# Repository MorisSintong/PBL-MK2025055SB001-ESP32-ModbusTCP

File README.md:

# PBL-MK2025055SB001 - Face Detection & Assembly Station SCADA

Project-Based Learning (PBL) repository for a SCADA prototype built around the
**Assembly Station** at Politeknik Negeri Batam (POLIBATAM). The system uses an
**ESP32-S3** and a **Mitsubishi FX5U PLC** as the main components, communicating
over **Modbus TCP/IP** through a W5500 Ethernet module, with a PC-based face
recognition interface acting as the human-machine interface (HMI) and access
controller.

The main objective is to develop an automatic control & monitoring system for
the Assembly Station that:

- Can be accessed over **Wi-Fi** by external devices (PC, mobile, HMI).
- Talks to the **FX5U PLC** via **Modbus TCP/IP** through the ESP32 (Modbus
  server on port 503).
- Performs **face recognition** on the PC (OpenCV/LBPH) and only allows
  authorized operators to start the machine.
- Provides a web HMI with live video feed, status indicators, and start/stop/\
  emergency/reset controls.
- Uses a modern **CMake + Ninja + Xtensa GCC 16.1.0** cross-compilation toolchain
  and host **CTest** simulation harness with zero dependency on PlatformIO or Arduino IDE.

## Repository Layout

| Path | Description |
| --- | --- |
| `Electrical-Schematics/` | KiCad project and rendered images of the electrical wiring (ESP32-S3 + W5500 + PLC I/O). |
| `ESP32-Program/` | Modular C++17 firmware for the ESP32-S3 (CMake + Ninja + Xtensa GCC 16.1.0 + FreeRTOS + Modbus TCP + CTest host suite). |
| `Emulation/` | Multi-node hardware emulation (Virtual ESP32 Bridge, Virtual FX5U PLC, Virtual HMI, Renode) & QoS benchmark suite. |
| `Interface/` | Python (Flask + OpenCV) face-recognition HMI, web front-end, and empirical timing logs (`Timings_log/`). |
| `justfile` | Root task runner orchestrating firmware builds, CTest unit tests, multi-node QoS emulation, and flashing. |
| `test_results.md` | Comprehensive test report compiling CTest unit tests, physical hardware baseline logs, and multi-node emulation QoS metrics. |
| `README.md` | High-level system architecture, repository layout, and quick-start guide. |

## System Architecture
```mermaid
graph TD
    Camera[Camera]
    PC[PC]
    PLC[PLC FX5U]
    Wago[Wago I/O Module]
    ExternalDevice[External Device]
    Output[Output]

    subgraph ESP32Container ["ESP32-S3 Physical Device"]
        ESP32Core(ESP32-S3)
        subgraph HostedServices ["Hosted Services"]
            WebServer[Web Server]
        end
    end

    Camera ---|USB-Serial| PC
    PC ---|HTTP Wi-Fi :80| ESP32Core
    Wago --- Output

    PLC ===|Modbus TCP/IP :503 PLC=Client, ESP32-S3=Server| ESP32Core
    PLC ===|Modbus TCP/IP PLC=Client, Wago=Server| Wago

    WebServer -.->|Wi-Fi| ExternalDevice
```

## System Overview

1. **Interface (PC)** runs a Flask web app (`Interface/app.py` or `Interface/AppImproved.py`) that:
   - Captures the webcam feed and detects faces using Haar cascade.
   - Recognizes the operator using an LBPH model (`trainer/trainer.yml`).
   - On authorized detection, sends HTTP commands to the ESP32
     (`/action?type=start|stop|emergency|reset`) and updates `/user_detection?detected=1|0`.
2. **ESP32-S3** (`ESP32-Program/App/Src/main.cpp`) runs the Modbus bridge & REST gateway:
   - **Wi-Fi & REST API (Core 0)** — receives commands from the PC interface on port 80.
   - **W5500 Ethernet & Modbus TCP server (Core 1)** — serves Modbus TCP on port 503, writes momentary command coils read by the FX5U PLC, and reads status feedback coils from the PLC.
3. **Mitsubishi FX5U PLC** is the Modbus TCP client that controls the Assembly
   Station actuators based on the ESP32 coils.

See the [System Architecture](#system-architecture) section for the full block diagram and the per-directory
`README.md` files for component-level details.

## Quick Start

1. Test, emulate, and flash the firmware using the modern toolchain (`just` + CMake + Ninja + Xtensa GCC / MinGW Clang):
   ```bash
   just test                     # Run host CTest unit test suite (0.04s)
   just build-release            # Cross-compile native ESP32-S3 ELF & firmware.bin
   just emulate-qos samples="50" # Run multi-node SCADA & PLC QoS emulation
   just diag-esptool             # Run silicon flash & security diagnostics on COM10
   just flash-esptool            # Flash ESP32-S3 over UART via uvx esptool @ 921600 baud
   just monitor                  # Serial monitor @ 921600 baud via uvx pyserial
   ```
2. Train the face model from the PC interface:
   ```bash
   cd Interface
   python 01_Ambil_Wajah.py   # capture dataset into dataset/
   python 02_training.py      # train -> trainer/trainer.yml
   ```
3. Launch the web HMI:
   ```bash
   python app.py              # http://<PC-IP>:5000
   ```
4. Configure the PLC (FX5U) Modbus TCP client to connect to the ESP32 Ethernet
   IP (`192.168.1.50:503`) and read/write the coils listed in
   `ESP32-Program/App/Inc/app_config.hpp`.

## Finished Product & Implementation

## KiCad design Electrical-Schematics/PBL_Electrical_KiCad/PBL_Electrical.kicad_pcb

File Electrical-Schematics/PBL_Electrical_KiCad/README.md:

# PBL_Electrical_KiCad

Native KiCad project for the PBL Assembly Station electrical schematic and PCB.

## Preview

## Key files

- `PBL_Electrical.kicad_pro` – KiCad project file (open this in KiCad).
- `PBL_Electrical.kicad_sch` – Schematic sheet.
- `PBL_Electrical.kicad_pcb` – PCB layout.
- `PBL_Electrical.kicad_prl` – KiCad project local settings.
- `PBL_Proj.bak` / `PBL_Proj-sem5.pretty/` / `PBL_Proj.kicad_sym` – Project
  symbol library, custom footprint library, and backups.
- `fp-info-cache`, `fp-lib-table`, `sym-lib-table` – KiCad library tables.
- `PBL_Electrical.png` – Rendered preview of the board/schematic.
- `PBL_Electrical.step` / `PBL_Electrical.wrl` – 3D model exports for CAD.
- `3d.pcb3d` – KiCad 3D viewer cache.
- `PBL_Electrical-backups/` – Automatic KiCad backups.

## How to use

1. Open `PBL_Electrical.kicad_pro` in **KiCad 6+**.
2. Edit the schematic / PCB as needed.
3. Re-export `PBL_Electrical.png` and the 3D models, then update the parent
   `Electrical-Schematics/` images if the wiring changes.

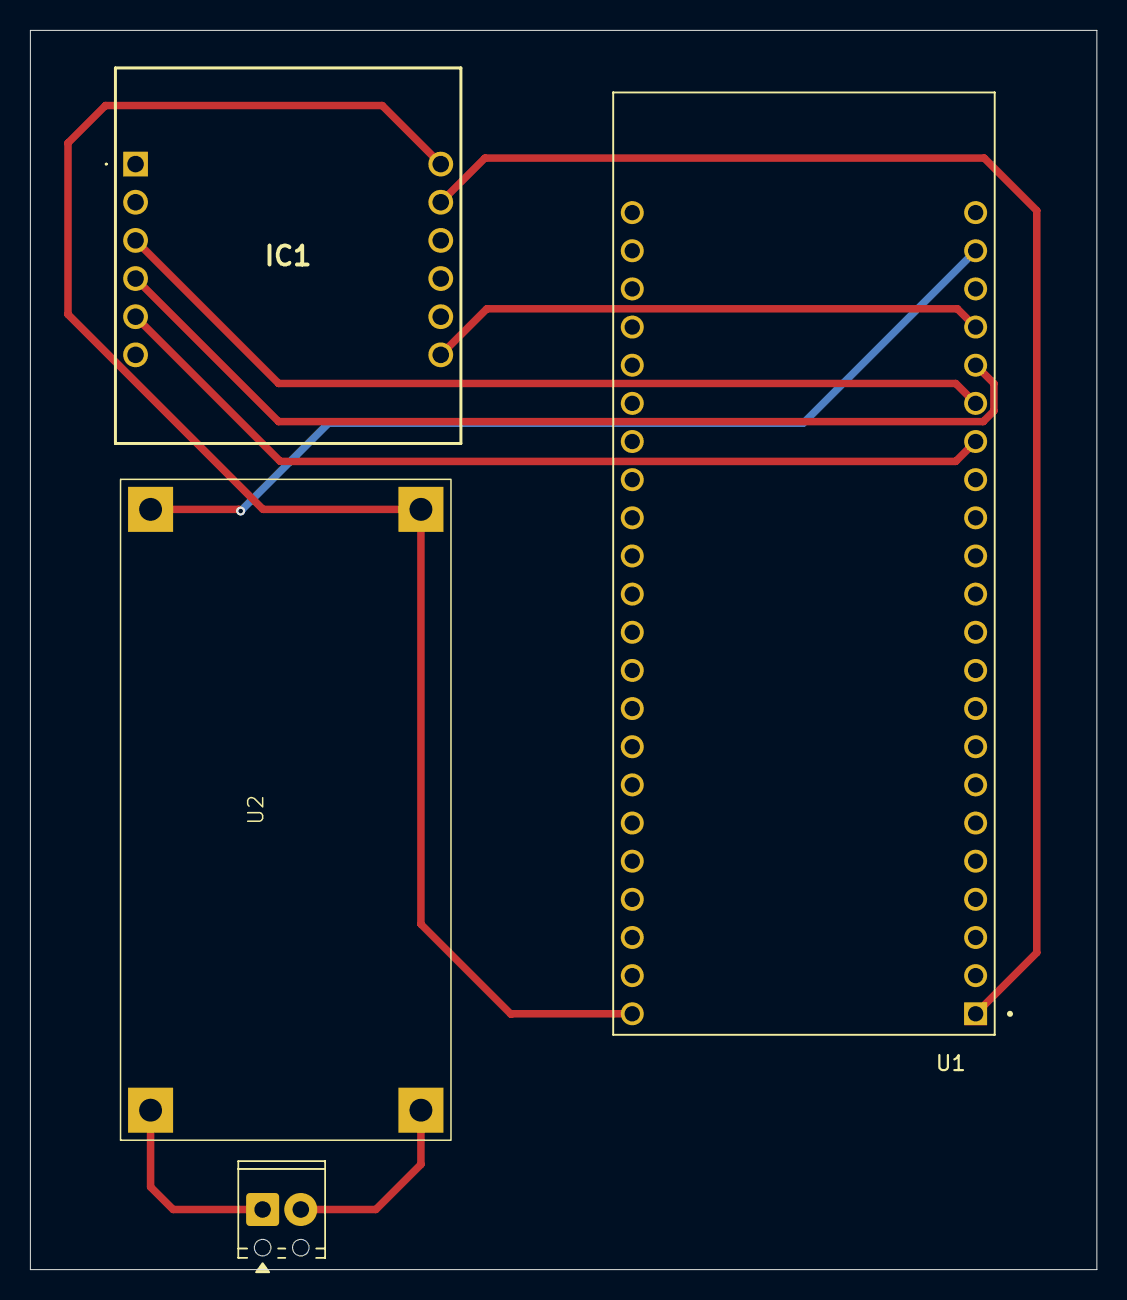
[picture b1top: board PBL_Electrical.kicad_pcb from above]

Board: 2 copper layers, 71.0 x 82.5 mm, 4 parts (0 on the bottom side), 9 nets.

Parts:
IC1: w5500 Module; WIZ850IO
J1: Screw_Terminal_01x02; TerminalBlock_Phoenix_MPT-0,5-2-2.54_1x02_P2.54mm_Horizontal
U1: ESP32-S3-DEVKITC-1-N16R8; ESP32-S3-DEVKITC-1-N8R8
U2: LM2586S Buck-Converter; Untitled

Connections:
+3V3: IC1.J22 (3.3V_1), U1.J1_1 (3V3)
+5V: U1.J1_21 (5V0), U2.3 (OUT+)
+24V: J1.1, U2.1 (IN+)
/ETH_CS: IC1.J15 (SCNN), U1.J1_16 (GPIO10)
/ETH_MISO: IC1.J26 (MISO), U1.J1_19 (GPIO13)
/ETH_MOSI: IC1.J13 (MOSI), U1.J1_17 (GPIO11)
/ETH_SCLK: IC1.J14 (SCLK), U1.J1_18 (GPIO12)
GND: IC1.J21 (GND_3), U1.J3_1 (GND), U2.4 (OUT-)
GND1: J1.2, U2.2 (IN-)

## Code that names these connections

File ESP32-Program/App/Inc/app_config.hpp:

#pragma once

#include <cstddef>
#include <cstdint>

namespace pbl {
namespace config {

// =======================================================================
// HARDWARE SPI & W5500 PIN CONFIGURATION (ESP32-S3)
// =======================================================================
constexpr uint8_t ETH_CS_PIN = 10;
constexpr uint8_t ETH_MOSI_PIN = 11;
constexpr uint8_t ETH_SCLK_PIN = 12;
constexpr uint8_t ETH_MISO_PIN = 13;

// SPI Frequency for W5500: 8 MHz for maximum reliability in industrial
// multi-drop SPI
constexpr uint32_t ETH_SPI_FREQ_HZ = 8000000;

// =======================================================================
// ETHERNET NETWORK CONFIGURATION
// =======================================================================
constexpr uint8_t ETH_MAC[6] = {0x02, 0xAB, 0xCD, 0x01, 0x02, 0x03};

// Static IP: 192.168.1.50
constexpr uint8_t ETH_IP[4] = {192, 168, 1, 50};
constexpr uint8_t ETH_GATEWAY[4] = {192, 168, 1, 1};
constexpr uint8_t ETH_SUBNET[4] = {255, 255, 255, 0};
constexpr uint8_t ETH_DNS[4] = {192, 168, 1, 1};

constexpr uint16_t ETH_TIMEOUT_MS = 200; // Retransmission timeout (ms)
constexpr uint8_t ETH_RETRIES = 4;       // Retransmission count

// =======================================================================
// MODBUS TCP CONFIGURATION (MITSUBISHI FX5U PLC INTERFACE)
// =======================================================================
constexpr uint16_t MODBUS_TCP_PORT = 503;

// Command Coils (PC Interface -> ESP32 -> PLC)
constexpr uint16_t COIL_BTN_START = 112;     // Momentary Start
constexpr uint16_t COIL_BTN_STOP = 113;      // Momentary Stop
constexpr uint16_t COIL_BTN_EMERGENCY = 114; // Momentary Emergency Stop
constexpr uint16_t COIL_BTN_RESET = 115;     // Momentary Fault Reset
constexpr uint16_t COIL_USER_DETECTED =
    116; // Continuous Latch (Face Recognition)

// Status Coils (PLC -> ESP32 -> PC Interface)
constexpr uint16_t COIL_STS_RUNNING = 208; // Machine is running
constexpr uint16_t COIL_STS_STOPPED = 209; // Machine is stopped
constexpr uint16_t COIL_STS_EMG = 210;     // Emergency active

// Register Table Allocation Limits
constexpr uint16_t MODBUS_COIL_COUNT = 300;
constexpr uint16_t MODBUS_HREG_COUNT = 300;

// Pulse timing for momentary command coils (milliseconds)
constexpr uint32_t MOMENTARY_PULSE_DURATION_MS = 500;

// =======================================================================
// WI-FI & REST API CONFIGURATION
// =======================================================================
constexpr const char *WIFI_SSID = "TestEsp32";
constexpr const char *WIFI_PASSWORD = "12345678";

// Wi-Fi Static IP: 10.251.64.200
constexpr uint8_t WIFI_IP[4] = {10, 251, 64, 200};
constexpr uint8_t WIFI_GATEWAY[4] = {10, 251, 64, 8};
constexpr uint8_t WIFI_SUBNET[4] = {255, 255, 255, 0};
constexpr uint8_t WIFI_DNS[4] = {10, 251, 64, 8};

constexpr const char *MDNS_HOSTNAME = "esp32-server";
constexpr uint16_t WEB_SERVER_PORT = 80;

// =======================================================================
// DIAGNOSTIC & SUPERVISION INTERVALS (MILLISECONDS)
// =======================================================================
constexpr uint32_t ETH_LINK_CHECK_INTERVAL_MS = 2000;
constexpr uint32_t ETH_SOCKET_CHECK_INTERVAL_MS = 3000;
constexpr uint32_t WIFI_RECONNECT_INTERVAL_MS = 10000;

// =======================================================================
// FREERTOS TASK ALLOCATION
// =======================================================================
constexpr uint32_t TASK_STACK_SIZE_BYTES = 8192;

constexpr uint32_t MODBUS_TASK_CORE = 1;     // App Core (Fast Modbus execution)
constexpr uint32_t MODBUS_TASK_PRIORITY = 2; // High priority

constexpr uint32_t WIFI_TASK_CORE = 0;     // Pro Core (Network stack & HTTP)
constexpr uint32_t WIFI_TASK_PRIORITY = 1; // Normal priority

constexpr uint32_t SERIAL_BAUD_RATE = 921600;

} // namespace config
} // namespace pbl

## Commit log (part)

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2026-04-24 file PBL Sem 5
2026-04-24 Initialize README with project description
    Added project overview and objectives for the SCADA system prototype.
2026-04-27 Menambahkan file Interface
2026-04-27 Add README for Modbus TCP/IP Bridge program
    Added a README file explaining the Modbus TCP/IP Bridge program for ESP32-S3.
2026-06-26 added detailed explanations
2026-06-26 added real-life photos
2026-06-28 Mermaid systems block diagram implementation
2026-06-28 fixed memrmaid styling.
2026-06-28 fixed entries on readme.md
